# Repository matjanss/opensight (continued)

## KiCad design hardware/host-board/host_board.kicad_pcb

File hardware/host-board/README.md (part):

# Host board v0.3: schematic and board

The host board for the acoustic target: a NodeMCU-32S, 8 sensor connectors, the IR curtain emitter and receiver, an air sensor (BME280 or DS18B20), and the panel LED and button. Every part is through-hole and hand-soldered. The board is 76 × 132 mm (the long side runs north–south), 2 layers, 1.6 mm thick, with an M3 mounting hole in each corner.

The files are in KiCad 10 format; open them with KiCad 10 or newer. "Update PCB from Schematic" reports no changes.

**Not ordered yet; ready to order** (2026-11-24). The two changes below are on the board now,
and the south half was laid out again with them (see [Layout](#layout)):

1. J5 takes a BME280 as well as the DS18B20. See [A BME280 on J5](#1-a-bme280-on-j5).
2. The curtain comparator U4 has a supply jumper: 3.3 V for a TLC372, 5 V for an LM393, with its own decoupling. See [The curtain comparator's supply](#2-the-curtain-comparators-supply-33-v-or-5-v-by-a-jumper).

## Changes before ordering (done)

### 1. A BME280 on J5

**Why:** the speed of sound depends on humidity as well as temperature:

- 0.011 m/s per % RH at 18 °C, and 0.017 at 25 °C;
- 30 → 60 % RH is about 0.08 mm rms of shot position (0.12 mm at 25 °C);
- pressure has almost no effect (100 hPa ≈ 0.01 mm).

The DS18B20 can't see humidity. A BME280 (temperature, humidity and pressure, over I2C) can. Its temperature is no more accurate than the DS18B20's (±0.5 °C); humidity is the gain. See `../../PLAN.md` (D8).

**The change:**

1. **J5:** a 4-pin JST XH (B4B-XH-A) instead of the 3-pin. Pins 1–3 stay as they are, so a DS18B20 cable still plugs into pins 1–3.

   | J5 pin | Now (v0.3) | New |
   |---|---|---|
   | 1 | GND | GND |
   | 2 | DQ: GPIO 14 (U2 pin 12) | SDA, or the DS18B20's DQ: GPIO 14 (U2 pin 12) |
   | 3 | +3V3 (the NodeMCU's 3V3, U2 pin 1) | +3V3 (unchanged) |
   | 4 | – | SCL: GPIO 15 (U2 pin 35) |

2. **R45, new:** 4.7 k from +3V3 to GPIO 15, the SCL pull-up, next to R43. R43 (4.7 k, +3V3 to GPIO 14) stays: it is the SDA pull-up, and the DS18B20's pull-up.
3. **GPIO 12 stays unconnected, with no pull-up.** The firmware moves the pulse generator's sync loopback from GPIO 15 to GPIO 12. GPIO 12 is the flash-voltage strapping pin: anything holding it high at boot stops the module from starting.
4. **Silkscreen:** J5 "BME280 / DS18B20", with pin labels GND, SDA, 3V3, SCL.
5. **Status (2026-11-23):** done in the schematic and the parts list. J5 has its own symbol,
   `CONN4_AIR` (pins GND, SDA/DQ, VDD, SCL), in `host_board.kicad_sym`; the net DQ is now
   `SDA_DQ`, and GPIO 15 is on the new net `SCL`. R45 has R43's footprint (horizontal,
   7.62 mm). ERC: 0 violations. **On the board (2026-11-24):** J5's 4-pin footprint beside J6
   and J7, turned so pin 1 (GND) is at its east end; R45 under the NodeMCU between R43 and
   R44; the silkscreen; the PDFs.

**The sensor and its cable:**

- A BME280 breakout (GY-BME280 or similar), run from 3.3 V.
- Buy carefully: many "BME280" modules are really BMP280s, which have no humidity. The firmware reports the chip ID: 0x60 is a BME280, 0x58 a BMP280.
- Breakouts usually have the pin order VCC, GND, SCL, SDA, which doesn't match J5 one to one: wire the cable by signal name.
- Keep the cable short, up to about 50 cm (I2C at 100 kHz). Many breakouts have their own 10 k pull-ups; with R43 and R45 in parallel that's about 3.2 k, which is fine.
- Mount the sensor in the air between the mics, away from the host board and the IR LEDs, which warm it.

**Firmware:** done in measurement step 3a. The sync loopback is on GPIO 12 (`SYNC_PIN` in
`config.h`); `airtemp.cpp` looks for a BME280 or BMP280 on I2C (SDA 14, SCL 15), else a
DS18B20 on GPIO 14; the speed of sound has the humidity term. Its bench tests with the real
sensors (MEASUREMENT 3a-3, 3a-4) wait for the parts.

### 2. The curtain comparator's supply: 3.3 V or 5 V, by a jumper

**Why:** U4 runs from VA_IR, 3.3 V. Its inputs have to work up to the threshold: RV1 sets
VTH_IR to 1.71–2.35 V (R41 1.5 k, RV1 1 k, R42 2.7 k), and VMID_IR is 1.65 V. When a shadow
lifts the + input past a threshold that is out of the input range, both inputs are out of
range at the crossing, and the comparator's output isn't guaranteed: it can switch late or
not at all.

- **The LM393** (as designed): inputs up to Vcc − 1.5 V, so 1.8 V at 3.3 V (25 °C; Vcc − 2.0
  V = 1.3 V over its temperature range). All but the bottom 90 mV of RV1's travel is out of
  range, and VMID_IR is only 0.15 V below the limit. **At 3.3 V the LM393 doesn't work.**
- **The TLC372CP** (TI CMOS, LM393 pinout, open drain, 200 ns, €1.95 at Okaphone): inputs up
  to Vdd − 1 V at 25 °C, so 2.3 V at 3.3 V; about 2.1–2.3 V at 15–25 °C indoors. TI
  guarantees only Vdd − 1.5 V (1.8 V) over its 0–70 °C range, and characterises it at 5 V
  (it is rated from 3 V). At 3.3 V it works with TP6 (VTH_IR) up to about 2.1 V: VMID_IR +
  450 mV, most of RV1's travel.
- **A TLV3202 on a SOIC-8 to DIP-8 adapter** (the sensor board's comparator: inputs beyond
  both rails, push-pull, 40 ns, 2.7–5.5 V, the LM393's pinout) works at 3.3 V without limits.
  It isn't sold by Dutch shops: it comes from LCSC.

So U4's supply gets a jumper: **3.3 V** for the TLC372 (or the TLV3202), **5 V** for the
LM393. Start with the TLC372 at 3.3 V; if RV1's sweep on the bench (see [TODO.md](TODO.md))
shows it running out of input range, plug in an LM393 and move the jumper to 5 V. See
[Buying U3 and U4](#buying-u3-and-u4-in-the-netherlands) for the parts.

**The change:**

1. **JP1, new:** a 1x3 pin header (2.54 mm) with a jumper shunt, next to U4. Its middle pin
   is U4 pin 8 (V+, a new net `VU4`):
   - pin 1: **VA_IR** (3.3 V): the TLC372, or the TLV3202;
   - pin 3: **VCMP** (about 4.7 V, below): the LM393.

   Silkscreen: "U4 SUPPLY", with "3V3 (TLC372)" and "5V (LM393)" at the ends.
2. **VCMP, a new net** fed from 5V_F (the LP2950's input, after the Schottky):
   - **R46, new:** 10 Ω from 5V_F to VCMP;
   - **C18, new:** 10 µF electrolytic from VCMP to AGND.

   With R46 that is a 1.6 kHz low-pass against the USB rail's noise.
3. **C17 moves with pin 8:** it is U4's 100 nF already (pin 8 to pin 4, AGND), so it now
   decouples VU4, whichever supply is chosen. No new capacitor.
4. **Everything else stays on VA_IR:** U3, VMID_IR, the threshold divider and RV1, and C16
   (U3's 100 nF). The threshold always comes from the quiet 3.3 V.
5. **The output stays as it is:** open collector (LM393) or open drain (TLC372), pulled up to
   +3V3 by R40, so GPIO 13 never sees more than 3.3 V. With a push-pull part (the TLV3202) R40
   only draws 0.33 mA while the output is low, but then the jumper must be at 3.3 V: a
   push-pull output at 5 V would drive GPIO 13 to 5 V. R39 (1 M, the hysteresis) and R38
   are unchanged.
6. **U4 unit B (unused)** stays as it is: + (pin 5) at AGND, − (pin 6) at VA_IR, output (pin
   7) open. Its inputs are inside the range of each part at either supply, except the LM393
   at 3.3 V, which isn't used.
7. **Status (2026-11-23):** done in the schematic and the parts list. JP1 has its own symbol,
   `JMP1x3` (a 1x3 header with the pins named 3V3, U4, 5V), in `host_board.kicad_sym`. ERC: 0
   violations. U4's value is now TLC372. **On the board (2026-11-24):** R46 beside NT1 where
   the supplies cross into AGND, JP1 north of U4 with C18, C17 at U4's pin 8; the
   silkscreen; the PDFs.

**The ranges, per setting:**

| U4 | Jumper | Inputs work up to | RV1's travel (TP6 1.71–2.35 V) |
|---|---|---|---|
| TLC372CP | 3.3 V | about 2.3 V (25 °C), 1.8 V guaranteed (0–70 °C) | up to about 2.1 V: most of it |
| TLV3202 on an adapter | 3.3 V (never 5 V) | 3.5 V | all |
| LM393N | 5 V | about 2.9–3.5 V (25 °C), 2.4–3.0 V over temperature (VCMP 4.4–5.0 V: USB 4.75–5.25 V less the Schottky) | all |
| LM393N | 3.3 V | 1.8 V | **don't use** |

The amplifier's output can reach 3.3 V, above some of these ranges. That's fine: the output
stays right as long as one input (here the threshold) is inside the range. No input goes above
U4's supply.

**Speed:** fast enough with each. The chain from a shadow to IR_IN rising is about 3–8 µs:
the TIA about 1 µs, the ×21 stage about 3.3 µs (τ; the MCP6002's 1 MHz is the slowest part),
the comparator 0.2 µs (TLC372, 10 mV overdrive) or 0.3–1.3 µs (LM393, faster with more
overdrive), R40's rise about 0.2 µs. That delay moves every dip later, so the curtain's window
(`curtain window`, 45–100 µs now) is set from the bench test of the real curtain; a slow air
pistol pellet (150 m/s) is already at 100 µs.

**Also note:** C13 (3.3 nF) into R35 (10 k) is a 33 µs high-pass. During a 30–40 µs shadow the
signal sinks back toward VMID_IR, so the comparator falls early: the dip lengths in the
firmware's `rec` lines (`ir=rise/len`) are shorter than the real shadow. The rise, which the
gate uses, is not affected.

## Changes from v0.2

- The BAT85 clamp diodes are gone; the ESP32's own input clamps and the 470 Ω series resistors protect the inputs.
- The 1x20 debug row (J8) is replaced by a 1x3 scope header per channel (J21–J28: H, GND, L), next to the channel's resistors.
- New GPIO map: the H line of each channel is on the northern pin of its pair, so no line crosses another between the module and the connector.
- IR_EN moved from GPIO16 to GPIO27, DQ (DS18B20) from GPIO17 to GPIO14.
- Rectangular board with a new layout (below).

## Files

- `host_board.kicad_pro`, `.kicad_sch`, `.kicad_pcb`: the project, the schematic (one A2 sheet) and the board.
- `host_board_schematic.pdf`: the schematic as a PDF.
- `host_board_assembly.pdf`: the assembly drawing, with every reference on its part (for soldering).
- Gerbers and drill files are not in the repo: plot them from the board in KiCad when ordering (they are made from it, and go stale with every change to it).
- `host_board_parts_list.csv`: every part, with how many to fit for a 6-channel first build.
- `host_board.pretty/`: the NodeMCU-32S footprint (two 1x19 sockets, rows 22.86 mm apart, from your 23.53 mm measurement over the outside of the pins).
- `host_board.3dshapes/`: the NodeMCU-32S on its sockets as a 3D model (boxes, made by `make_nodemcu.py`), used by U2's footprint.
- `mechanical/`: the board as STEP and STL for the enclosure, with the sizes that matter (see its README).

## Layout

North is the antenna end of the NodeMCU. The north half (the module and the eight channels)
is as it was; the south half was laid out again on 2026-11-24, 14 mm longer, for the J5 and
U4-supply changes and with room for 0.4 mm tracks.

| Where | What |
|---|---|
| Middle, north half | The NodeMCU-32S on sockets, antenna at the north edge, USB plug pointing south (the area south of it is kept free for the plug). No copper under the antenna (a keep-out on both layers) |
| West edge | Sensors CH1–CH4 (J11–J14), north to south. Beside each one: scope header J2n and the four channel resistors |
| East edge | Sensors CH5–CH8 (J15–J18), mirrored |
| Under the NodeMCU | R43 (SDA pull-up), R45 (SCL pull-up), R44 (panel LED), lying flat |
| South of the module, west | The sensor supply: R1 and C3/C4 (5 V filter), U1 LP2950, C5/C6, TP2 (VSENS). R40 (IR_IN pull-up). Then the row where the supplies cross into the receiver's AGND: R30 (VA_IR), NT1 (the ground link), R46 (VCMP) |
| South of the module, east | J6 panel LED and J7 panel button, J5 air sensor (BME280 / DS18B20) below them |
| South-west | IR receiver on its own AGND copper, outlined: U4 (comparator) with JP1, C17, C18 and the threshold (RV1, TP6) in the north; U3 (TIA and ×21 stage) in the south, with J4 photodiodes at the south edge. Test loops TP3 AGND, TP4 TIA, TP5 AMP, TP6 VTH |
| East, south of CH8 | Power: J1 5 V in and J2 panel switch on the east edge, D1, C1, C2, test loops TP1 (+5V), TP7 (GND) |
| South-east | IR emitter: four current limiters side by side (R2.2k, BC337, BC547, R22 each), R29, C7, J3 IR LEDs at the south edge |

Connector pinout (every sensor connector the same way round): VA at the south end, then G, L, G, H at the north end. The scope header pins H, G, L sit level with connector pins H, G, L.

- **Under the NodeMCU:** R43, R44 and R45 are mounted flat there. Solder them before you fit the sockets.
- **Sensor supply:** VSENS runs down each edge outside the sensor connectors, with a stub to
  each VA pin; the two buses meet at TP2 beside U1.
- **Ground:** GND is poured on both sides. The IR receiver has its own AGND pour, joined to GND only at NT1, a wire link or 0 Ω resistor on the north edge of the receiver area. Only the receiver's supplies (VA_IR through R30, VCMP through R46) and IR_IN cross that edge; no other net runs over the AGND copper.
- **Tracks:** 0.4 mm for signals; 0.6 mm for +3V3, VSENS, VA_IR, 5V_F, VCMP and VU4; 0.8 mm
  for VIN, VSW and +5V. Clearance 0.2 mm, vias 0.8/0.4 mm (the net classes in the project).

## Notes for assembly

- **Scope headers:** J21–J28 are optional; fit one when you want to probe a channel.
- **470 Ω resistors:** a wire link can replace any of them.
- **Standing parts:** resistors stand upright on a 2.54 mm pitch to fit 8 channels on the board.
- **Sockets:** use DIP-8 sockets for U3 (MCP6002) and U4 (TLC372, or LM393 with JP1 at 5 V), so either can be swapped (see [Buying U3 and U4](#buying-u3-and-u4-in-the-netherlands)).
- **NodeMCU sockets:** fit the two 1x19 female headers last.

## Buying U3 and U4 in the Netherlands

The curtain receiver's two ICs are both socketed, so a part can be swapped and compared on
the bench. These are the DIP-8 parts found at consumer shops on 2026-11-23. Prices include
21 % VAT. Prices and stock change: check the shop's page before ordering. Okaphone's site
blocks automated visits, so its prices come from search results.

### U3: the op-amp (TIA and ×21 stage)

**Needs:** a dual in DIP-8 with the standard pinout, running from 3.3 V (VA_IR), with a
rail-to-rail output. The TIA's output sits below VMID_IR in steady light, and the ×21
stage's output rises toward 3.3 V on a shadow.

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
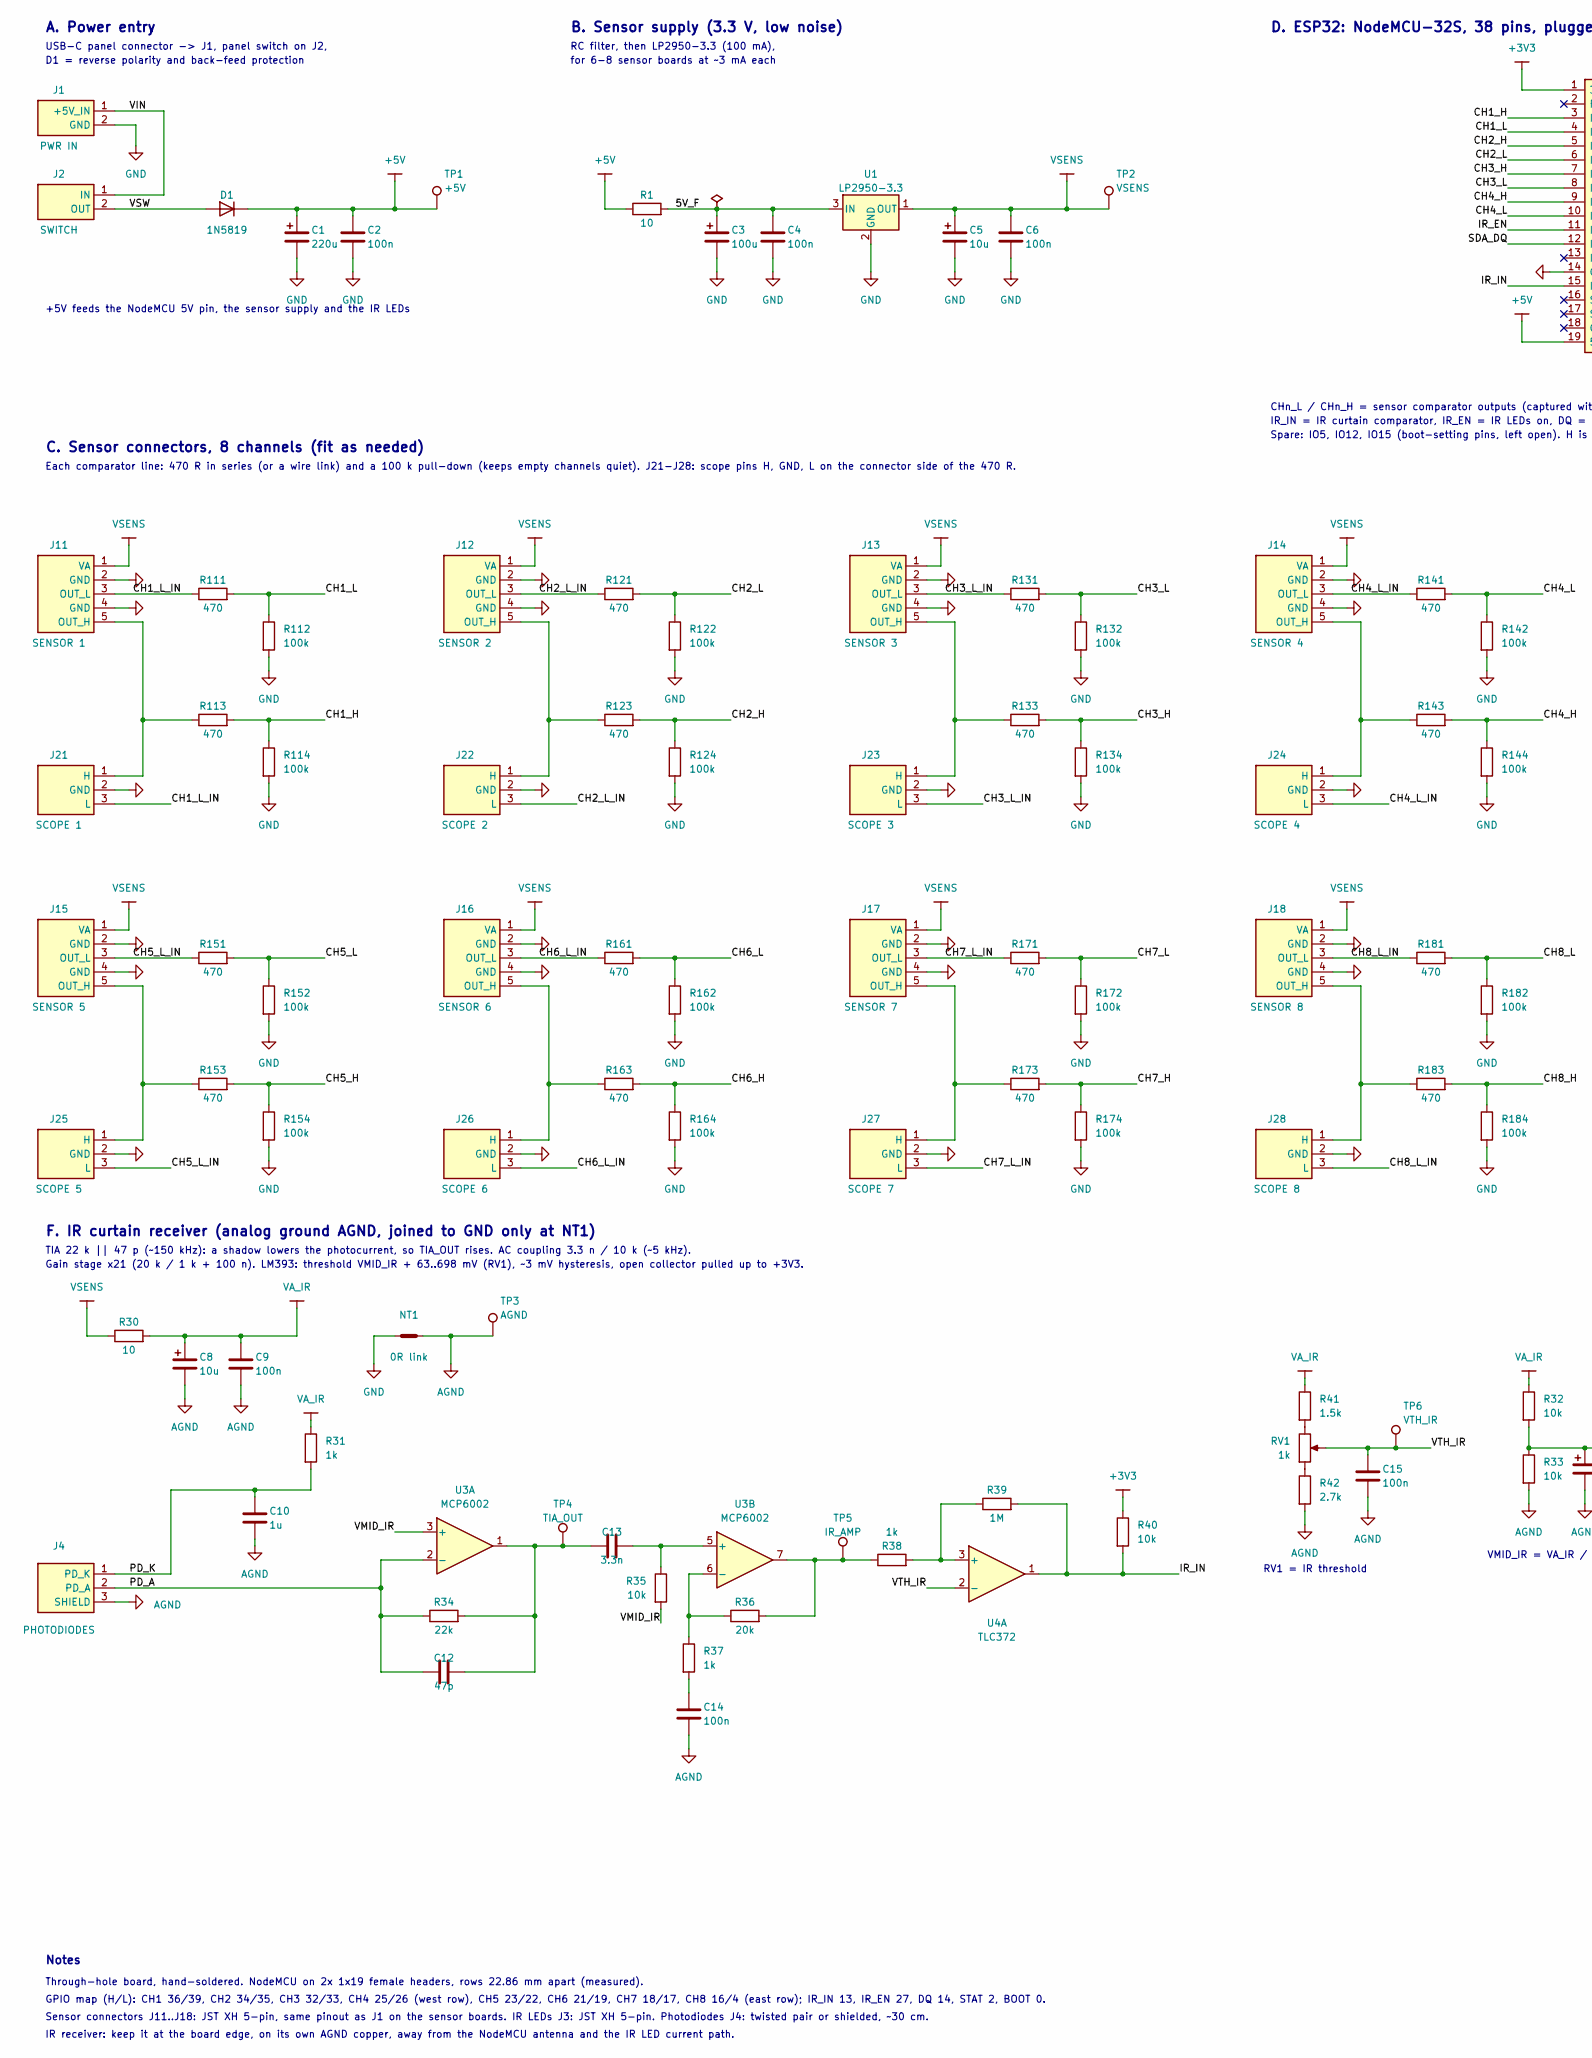
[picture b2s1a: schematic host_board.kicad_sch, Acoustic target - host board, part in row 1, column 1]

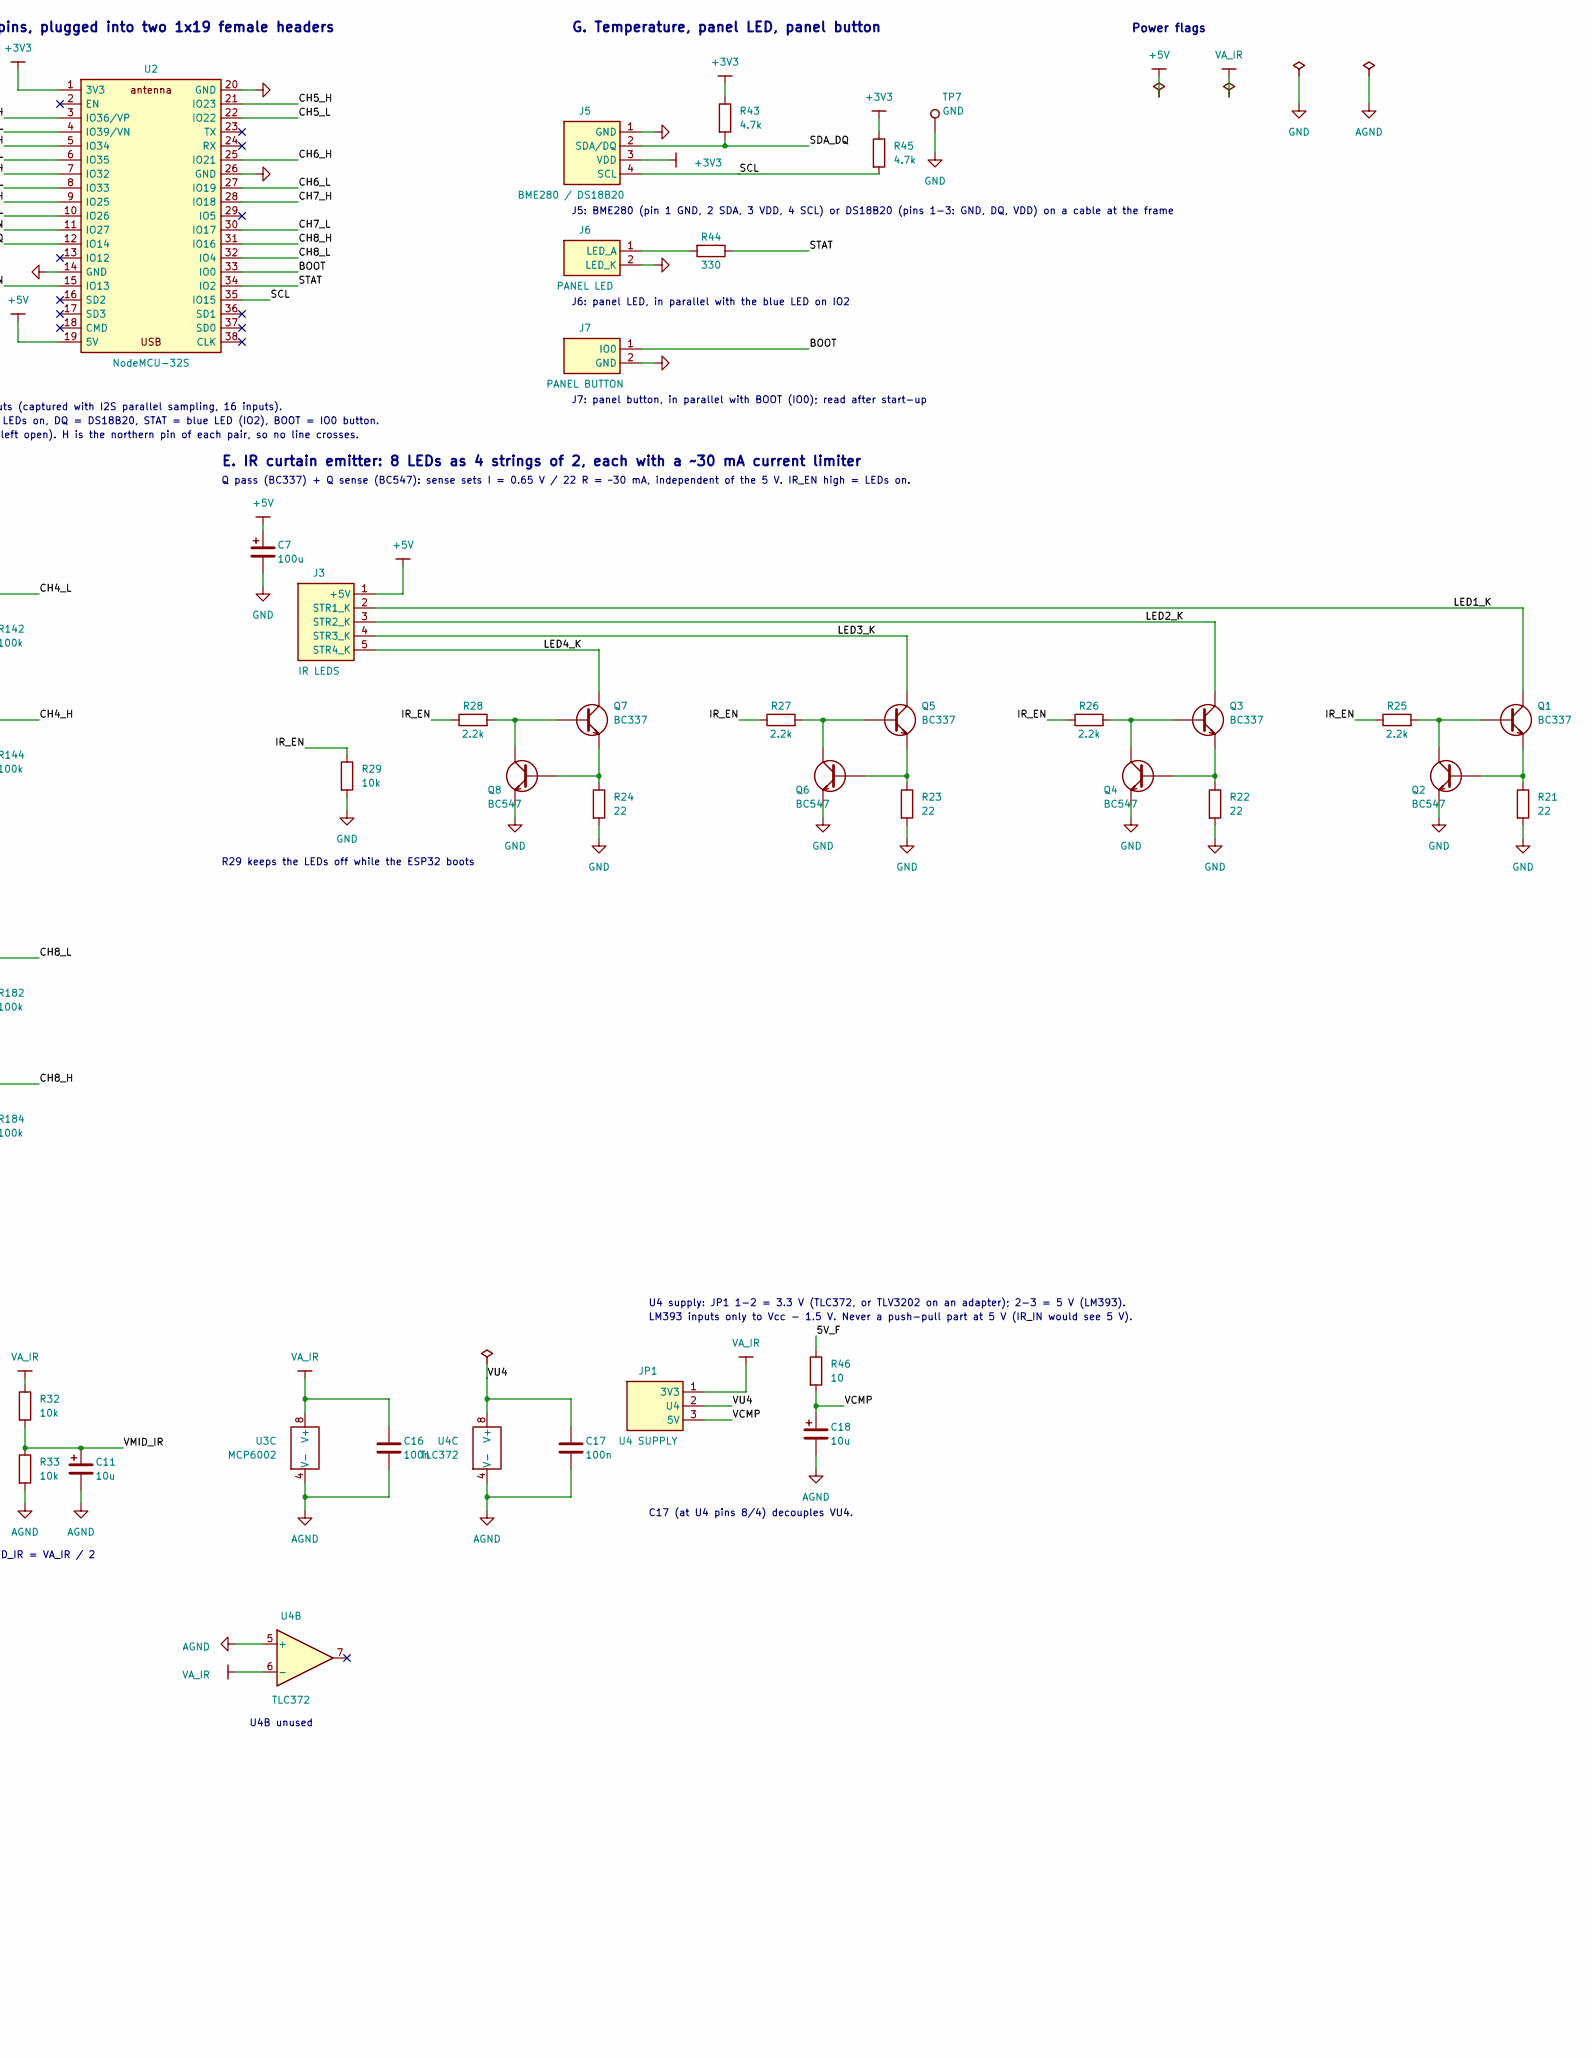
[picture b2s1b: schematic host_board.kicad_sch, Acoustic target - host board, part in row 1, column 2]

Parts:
C1: 220u; CP_Radial_D6.3mm_P2.50mm
C2, C4, C6, C9, C14, C15, C16, C17: 100n; C_Disc_D5.0mm_W2.5mm_P2.50mm
C3, C7: 100u; CP_Radial_D5.0mm_P2.00mm
C5, C8, C11, C18: 10u; CP_Radial_D5.0mm_P2.00mm
C10: 1u; C_Disc_D5.0mm_W2.5mm_P2.50mm
C12: 47p; C_Disc_D5.0mm_W2.5mm_P2.50mm
C13: 3.3n; C_Disc_D5.0mm_W2.5mm_P2.50mm
D1: 1N5819; D_DO-41_SOD81_P10.16mm_Horizontal
J1: PWR IN; JST_XH_B2B-XH-A_1x02_P2.50mm_Vertical
J2: SWITCH; JST_XH_B2B-XH-A_1x02_P2.50mm_Vertical
J3: IR LEDS; JST_XH_B5B-XH-A_1x05_P2.50mm_Vertical
J4: PHOTODIODES; JST_XH_B3B-XH-A_1x03_P2.50mm_Vertical
J5: BME280 / DS18B20; JST_XH_B4B-XH-A_1x04_P2.50mm_Vertical
J6: PANEL LED; JST_XH_B2B-XH-A_1x02_P2.50mm_Vertical
J7: PANEL BUTTON; JST_XH_B2B-XH-A_1x02_P2.50mm_Vertical
J11: SENSOR 1; JST_XH_B5B-XH-A_1x05_P2.50mm_Vertical
J12: SENSOR 2; JST_XH_B5B-XH-A_1x05_P2.50mm_Vertical
J13: SENSOR 3; JST_XH_B5B-XH-A_1x05_P2.50mm_Vertical
J14: SENSOR 4; JST_XH_B5B-XH-A_1x05_P2.50mm_Vertical
J15: SENSOR 5; JST_XH_B5B-XH-A_1x05_P2.50mm_Vertical
J16: SENSOR 6; JST_XH_B5B-XH-A_1x05_P2.50mm_Vertical
J17: SENSOR 7; JST_XH_B5B-XH-A_1x05_P2.50mm_Vertical
J18: SENSOR 8; JST_XH_B5B-XH-A_1x05_P2.50mm_Vertical
J21: SCOPE 1; PinHeader_1x03_P2.54mm_Vertical
J22: SCOPE 2; PinHeader_1x03_P2.54mm_Vertical
J23: SCOPE 3; PinHeader_1x03_P2.54mm_Vertical
J24: SCOPE 4; PinHeader_1x03_P2.54mm_Vertical
J25: SCOPE 5; PinHeader_1x03_P2.54mm_Vertical
J26: SCOPE 6; PinHeader_1x03_P2.54mm_Vertical
J27: SCOPE 7; PinHeader_1x03_P2.54mm_Vertical
J28: SCOPE 8; PinHeader_1x03_P2.54mm_Vertical
JP1: U4 SUPPLY; PinHeader_1x03_P2.54mm_Vertical
NT1: 0R link; R_Axial_DIN0207_L6.3mm_D2.5mm_P2.54mm_Vertical
Q1, Q3, Q5, Q7: BC337; TO-92_Inline
Q2, Q4, Q6, Q8: BC547; TO-92_Inline
R1, R30, R46: 10; R_Axial_DIN0207_L6.3mm_D2.5mm_P2.54mm_Vertical
R21, R22, R23, R24: 22; R_Axial_DIN0207_L6.3mm_D2.5mm_P2.54mm_Vertical
R25, R26, R27, R28: 2.2k; R_Axial_DIN0207_L6.3mm_D2.5mm_P2.54mm_Vertical
R29, R32, R33, R35, R40: 10k; R_Axial_DIN0207_L6.3mm_D2.5mm_P2.54mm_Vertical
R31, R37, R38: 1k; R_Axial_DIN0207_L6.3mm_D2.5mm_P2.54mm_Vertical
R34: 22k; R_Axial_DIN0207_L6.3mm_D2.5mm_P2.54mm_Vertical
R36: 20k; R_Axial_DIN0207_L6.3mm_D2.5mm_P2.54mm_Vertical
R39: 1M; R_Axial_DIN0207_L6.3mm_D2.5mm_P2.54mm_Vertical
R41: 1.5k; R_Axial_DIN0207_L6.3mm_D2.5mm_P2.54mm_Vertical
R42: 2.7k; R_Axial_DIN0207_L6.3mm_D2.5mm_P2.54mm_Vertical
R43, R45: 4.7k; R_Axial_DIN0207_L6.3mm_D2.5mm_P7.62mm_Horizontal
R44: 330; R_Axial_DIN0207_L6.3mm_D2.5mm_P7.62mm_Horizontal
R111, R113, R121, R123, R131, R133, R141, R143, R151, R153, R161, R163, R171, R173, R181, R183: 470; R_Axial_DIN0207_L6.3mm_D2.5mm_P2.54mm_Vertical
R112, R114, R122, R124, R132, R134, R142, R144, R152, R154, R162, R164, R172, R174, R182, R184: 100k; R_Axial_DIN0207_L6.3mm_D2.5mm_P2.54mm_Vertical
RV1: 1k; Potentiometer_Bourns_3296W_Vertical
TP1: +5V; TestPoint_Keystone_5000-5004_Miniature
TP2: VSENS; TestPoint_Keystone_5000-5004_Miniature
TP3: AGND; TestPoint_Keystone_5000-5004_Miniature
TP4: TIA_OUT; TestPoint_Keystone_5000-5004_Miniature
TP5: IR_AMP; TestPoint_Keystone_5000-5004_Miniature
TP6: VTH_IR; TestPoint_Keystone_5000-5004_Miniature
TP7: GND; TestPoint_Keystone_5000-5004_Miniature
U1: LP2950-3.3; TO-92_Inline
U2: NodeMCU-32S; NodeMCU-32S_38pin_Sockets_W22.86mm
U3: MCP6002; DIP-8_W7.62mm_Socket
U4: TLC372; DIP-8_W7.62mm_Socket

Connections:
+3V3: J5.3 (VDD), R40.1, R43.1, R45.1, U2.1 (3V3)
+5V: C1.1 (+), C2.1, C7.1 (+), D1.1 (K), J3.1 (+5V), R1.1, TP1.1 (1_1), U2.19 (5V)
/5V_F: C3.1 (+), C4.1, R1.2, R46.1, U1.3 (IN)
/BOOT: J7.1 (IO0), U2.33 (IO0)
/CH1_H: R113.2, R114.1, U2.3 (IO36/VP)
/CH1_L: R111.2, R112.1, U2.4 (IO39/VN)
/CH1_L_IN: J11.3 (OUT_L), J21.3 (L), R111.1
/CH2_H: R123.2, R124.1, U2.5 (IO34)
/CH2_L: R121.2, R122.1, U2.6 (IO35)
/CH2_L_IN: J12.3 (OUT_L), J22.3 (L), R121.1
/CH3_H: R133.2, R134.1, U2.7 (IO32)
/CH3_L: R131.2, R132.1, U2.8 (IO33)
/CH3_L_IN: J13.3 (OUT_L), J23.3 (L), R131.1
/CH4_H: R143.2, R144.1, U2.9 (IO25)
/CH4_L: R141.2, R142.1, U2.10 (IO26)
/CH4_L_IN: J14.3 (OUT_L), J24.3 (L), R141.1
/CH5_H: R153.2, R154.1, U2.21 (IO23)
/CH5_L: R151.2, R152.1, U2.22 (IO22)
/CH5_L_IN: J15.3 (OUT_L), J25.3 (L), R151.1
/CH6_H: R163.2, R164.1, U2.25 (IO21)
/CH6_L: R161.2, R162.1, U2.27 (IO19)
/CH6_L_IN: J16.3 (OUT_L), J26.3 (L), R161.1
/CH7_H: R173.2, R174.1, U2.28 (IO18)
/CH7_L: R171.2, R172.1, U2.30 (IO17)
/CH7_L_IN: J17.3 (OUT_L), J27.3 (L), R171.1
/CH8_H: R183.2, R184.1, U2.31 (IO16)
/CH8_L: R181.2, R182.1, U2.32 (IO4)
/CH8_L_IN: J18.3 (OUT_L), J28.3 (L), R181.1
/IR_EN: R25.1, R26.1, R27.1, R28.1, R29.1, U2.11 (IO27)
/IR_IN: R39.2, R40.2, U2.15 (IO13), U4.1
/LED1_K: J3.2 (STR1_K), Q1.1 (C)
/LED2_K: J3.3 (STR2_K), Q3.1 (C)
/LED3_K: J3.4 (STR3_K), Q5.1 (C)
/LED4_K: J3.5 (STR4_K), Q7.1 (C)
/PD_A: C12.1, J4.2 (PD_A), R34.1, U3.2 (-)
/PD_K: C10.1, J4.1 (PD_K), R31.2
/SCL: J5.4 (SCL), R45.2, U2.35 (IO15)
/SDA_DQ: J5.2 (SDA/DQ), R43.2, U2.12 (IO14)
/STAT: R44.1, U2.34 (IO2)
/VCMP: C18.1 (+), JP1.3 (5V), R46.2
/VIN: J1.1 (+5V_IN), J2.1 (IN)
/VMID_IR: C11.1 (+), R32.2, R33.1, R35.2, U3.3 (+)
/VSW: D1.2 (A), J2.2 (OUT)
/VTH_IR: C15.1, RV1.2, TP6.1 (1_1), U4.2 (-)
/VU4: C17.1, JP1.2 (U4), U4.8 (V+)
AGND: C8.2 (-), C9.2, C10.2, C11.2 (-), C14.2, C15.2, C16.2, C17.2, C18.2 (-), J4.3 (SHIELD), NT1.2, R33.2, R42.2, TP3.1 (1_1), U3.4 (V-), U4.4 (V-), U4.5 (+)
GND: C1.2 (-), C2.2, C3.2 (-), C4.2, C5.2 (-), C6.2, C7.2 (-), J1.2 (GND), J5.1 (GND), J6.2 (LED_K), J7.2 (GND), J11.2 (GND), J11.4 (GND), J12.2 (GND), J12.4 (GND), J13.2 (GND), J13.4 (GND), J14.2 (GND), J14.4 (GND), J15.2 (GND), J15.4 (GND), J16.2 (GND), J16.4 (GND), J17.2 (GND), J17.4 (GND), J18.2 (GND), J18.4 (GND), J21.2 (GND), J22.2 (GND), J23.2 (GND), J24.2 (GND), J25.2 (GND), J26.2 (GND), J27.2 (GND), J28.2 (GND), NT1.1, Q2.3 (E), Q4.3 (E), Q6.3 (E), Q8.3 (E), R21.2, R22.2, R23.2, R24.2, R29.2, R112.2, R114.2, R122.2, R124.2, R132.2, R134.2, R142.2, R144.2, R152.2, R154.2, R162.2, R164.2, R172.2, R174.2, R182.2, R184.2, TP7.1 (1_1), U1.2 (GND), U2.14 (GND), U2.20 (GND), U2.26 (GND)
unnamed: C12.2, C13.1, R34.2, TP4.1 (1_1), U3.1
unnamed: C14.1, R37.2
unnamed: J6.1 (LED_A), R44.2
unnamed: J11.5 (OUT_H), J21.1 (H), R113.1
unnamed: J12.5 (OUT_H), J22.1 (H), R123.1
unnamed: J13.5 (OUT_H), J23.1 (H), R133.1
unnamed: J14.5 (OUT_H), J24.1 (H), R143.1
unnamed: J15.5 (OUT_H), J25.1 (H), R153.1
unnamed: J16.5 (OUT_H), J26.1 (H), R163.1
unnamed: J17.5 (OUT_H), J27.1 (H), R173.1
unnamed: J18.5 (OUT_H), J28.1 (H), R183.1
unnamed: Q1.2 (B), Q2.1 (C), R25.2
unnamed: Q1.3 (E), Q2.2 (B), R21.1
unnamed: Q3.2 (B), Q4.1 (C), R26.2
unnamed: Q3.3 (E), Q4.2 (B), R22.1
unnamed: Q5.2 (B), Q6.1 (C), R27.2
unnamed: Q5.3 (E), Q6.2 (B), R23.1
unnamed: Q7.2 (B), Q8.1 (C), R28.2
unnamed: Q7.3 (E), Q8.2 (B), R24.1
unnamed: R36.2, R38.1, TP5.1 (1_1), U3.7
unnamed: R41.2, RV1.1
unnamed: R42.1, RV1.3
unnamed: C13.2, R35.1, U3.5 (+)
unnamed: R36.1, R37.1, U3.6 (-)
unnamed: R38.2, R39.1, U4.3 (+)
VA_IR: C8.1 (+), C9.1, C16.1, JP1.1 (3V3), R30.2, R31.1, R32.1, R41.1, U3.8 (V+), U4.6 (-)
VSENS: C5.1 (+), C6.1, J11.1 (VA), J12.1 (VA), J13.1 (VA), J14.1 (VA), J15.1 (VA), J16.1 (VA), J17.1 (VA), J18.1 (VA), R30.1, TP2.1 (1_1), U1.1 (OUT)

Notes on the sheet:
Through-hole board, hand-soldered. NodeMCU on 2x 1x19 female headers, rows 22.86 mm apart (measured).
D1 = reverse polarity and back-feed protection
RC filter, then LP2950-3.3 (100 mA),
J6: panel LED, in parallel with the blue LED on IO2
J5: BME280 (pin 1 GND, 2 SDA, 3 VDD, 4 SCL) or DS18B20 (pins 1-3: GND, DQ, VDD) on a cable at the frame
Sensor connectors J11..J18: JST XH 5-pin, same pinout as J1 on the sensor boards. IR LEDs J3: JST XH 5-pin. Photodiodes J4: twisted pair or shielded, ~30 cm.
J7: panel button, in parallel with BOOT (IO0); read after start-up
IR receiver: keep it at the board edge, on its own AGND copper, away from the NodeMCU antenna and the IR LED current path.
F. IR curtain receiver (analog ground AGND, joined to GND only at NT1)
D. ESP32: NodeMCU-32S, 38 pins, plugged into two 1x19 female headers
VMID_IR = VA_IR / 2
Spare: IO5, IO12, IO15 (boot-setting pins, left open). H is the northern pin of each pair, so no line crosses.
IR_IN = IR curtain comparator, IR_EN = IR LEDs on, DQ = DS18B20, STAT = blue LED (IO2), BOOT = IO0 button.
CHn_L / CHn_H = sensor comparator outputs (captured with I2S parallel sampling, 16 inputs).
Each comparator line: 470 R in series (or a wire link) and a 100 k pull-down (keeps empty channels quiet). J21-J28: scope pins H, GND, L on the connector side of the 470 R.
+5V feeds the NodeMCU 5V pin, the sensor supply and the IR LEDs
TIA 22 k || 47 p (~150 kHz): a shadow lowers the photocurrent, so TIA_OUT rises. AC coupling 3.3 n / 10 k (~5 kHz).
USB-C panel connector -> J1, panel switch on J2,
R29 keeps the LEDs off while the ESP32 boots
Gain stage x21 (20 k / 1 k + 100 n). LM393: threshold VMID_IR + 63..698 mV (RV1), ~3 mV hysteresis, open collector pulled up to +3V3.
Power flags
Q pass (BC337) + Q sense (BC547): sense sets I = 0.65 V / 22 R = ~30 mA, independent of the 5 V. IR_EN high = LEDs on.
GPIO map (H/L): CH1 36/39, CH2 34/35, CH3 32/33, CH4 25/26 (west row), CH5 23/22, CH6 21/19, CH7 18/17, CH8 16/4 (east row); IR_IN 13, IR_EN 27, DQ 14, STAT 2, BOOT 0.
B. Sensor supply (3.3 V, low noise)
U4B unused
G. Temperature, panel LED, panel button
C. Sensor connectors, 8 channels (fit as needed)
A. Power entry
RV1 = IR threshold
E. IR curtain emitter: 8 LEDs as 4 strings of 2, each with a ~30 mA current limiter
for 6-8 sensor boards at ~3 mA each
Notes
U4 supply: JP1 1-2 = 3.3 V (TLC372, or TLV3202 on an adapter); 2-3 = 5 V (LM393).
LM393 inputs only to Vcc - 1.5 V. Never a push-pull part at 5 V (IR_IN would see 5 V).
C17 (at U4 pins 8/4) decouples VU4.

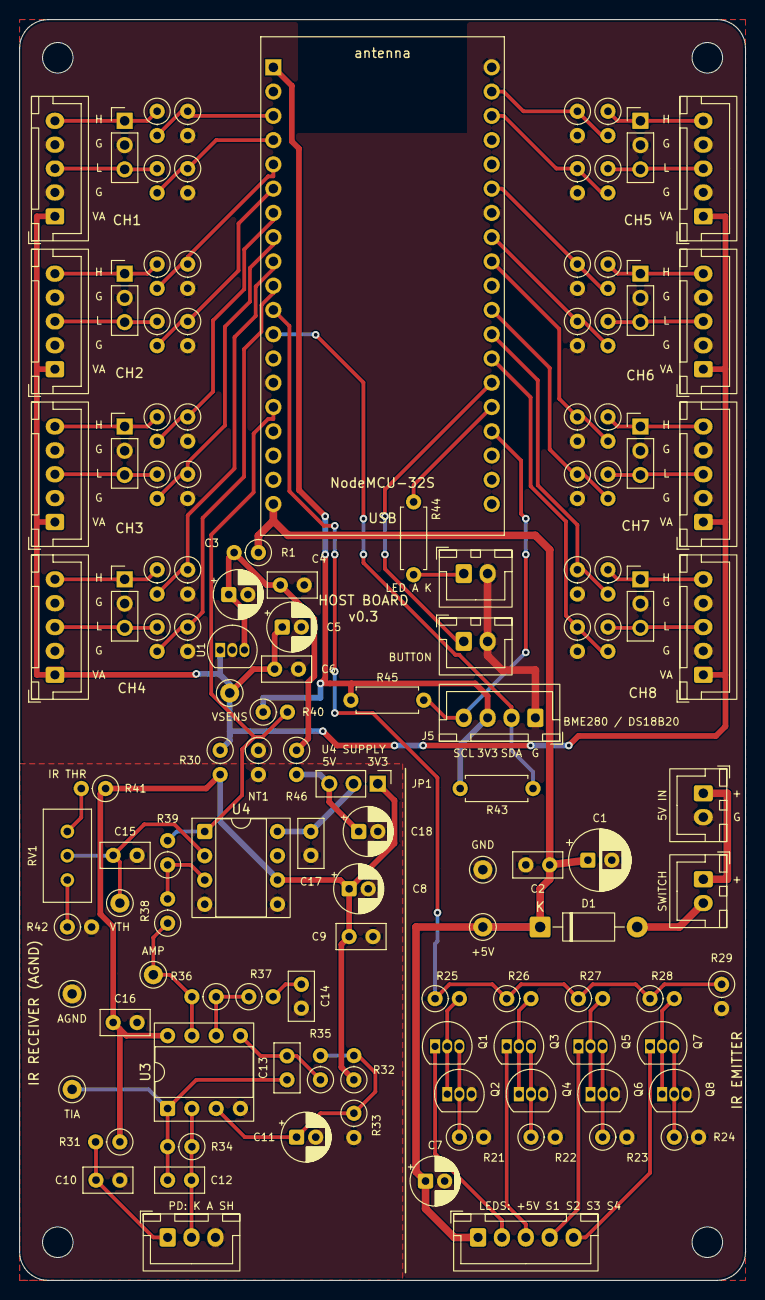
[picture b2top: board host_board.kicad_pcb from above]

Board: 2 copper layers, 76.0 x 132.0 mm, 127 parts (0 on the bottom side), 74 nets.

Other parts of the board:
H1, H2, H3, H4: M3; MountingHole_3.2mm_M3

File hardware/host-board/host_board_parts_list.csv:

References,Value,Part,On board,Fit for a 6-channel first build,Footprint,Notes
J1,PWR IN,JST XH vertical header (+ housing and crimps for the cable),1,1,JST_XH_B2B-XH-A_1x02_P2.50mm_Vertical,from USB-C panel connector
J2,SWITCH,JST XH vertical header (+ housing and crimps for the cable),1,1,JST_XH_B2B-XH-A_1x02_P2.50mm_Vertical,to panel on-off switch
D1,1N5819,diode,1,1,D_DO-41_SOD81_P10.16mm_Horizontal,reverse polarity / back-feed
C1,220u,"electrolytic capacitor, radial",1,1,CP_Radial_D6.3mm_P2.50mm,10 V electrolytic
"C2, C4, C6, C9, C14, C16, C17, C15",100n,"ceramic capacitor, 2.5 mm pitch",8,8,C_Disc_D5.0mm_W2.5mm_P2.50mm,at U3; at U4
TP1,+5V,Keystone 5000-series test loop,1,1,TestPoint_Keystone_5000-5004_Miniature,
"R1, R30, R46",10,"resistor 1/4 W 1 %, standing (2.54 mm)",3,3,R_Axial_DIN0207_L6.3mm_D2.5mm_P2.54mm_Vertical,
"C3, C7",100u,"electrolytic capacitor, radial",2,2,CP_Radial_D5.0mm_P2.00mm,10 V electrolytic
U1,LP2950-3.3,"LP2950ACZ-3.3 low-noise LDO, TO-92",1,1,TO-92_Inline,"LP2950ACZ-3.3, TO-92"
"C5, C8, C11, C18",10u,"electrolytic capacitor, radial",4,4,CP_Radial_D5.0mm_P2.00mm,16 V electrolytic
TP2,VSENS,Keystone 5000-series test loop,1,1,TestPoint_Keystone_5000-5004_Miniature,
"J11, J12, J13, J14, J15, J16, J17, J18",SENSOR 1-8,JST XH vertical header (+ housing and crimps for the cable),8,6,JST_XH_B5B-XH-A_1x05_P2.50mm_Vertical,fit as needed
"J21, J22, J23, J24, J25, J26, J27, J28",SCOPE 1-8,"1x3 pin header, 2.54 mm",8,0,PinHeader_1x03_P2.54mm_Vertical,"scope pins H, GND, L; fit only when needed"
"R111, R113, R121, R123, R131, R133, R141, R143, R151, R153, R161, R163, R171, R173, R181, R183",470,"resistor 1/4 W 1 %, standing (2.54 mm)",16,12,R_Axial_DIN0207_L6.3mm_D2.5mm_P2.54mm_Vertical,or wire link
"R112, R114, R122, R124, R132, R134, R142, R144, R152, R154, R162, R164, R172, R174, R182, R184",100k,"resistor 1/4 W 1 %, standing (2.54 mm)",16,12,R_Axial_DIN0207_L6.3mm_D2.5mm_P2.54mm_Vertical,
U2,NodeMCU-32S,"NodeMCU-32S (ESP32-WROOM-32), 38-pin; plus 2x 1x19 female header, 2.54 mm",1,1,NodeMCU-32S_38pin_Sockets_W22.86mm,plug-in module on 2x 1x19 female headers
J3,IR LEDS,JST XH vertical header (+ housing and crimps for the cable),1,1,JST_XH_B5B-XH-A_1x05_P2.50mm_Vertical,"8 x 940 nm, 4 strings of 2"
"R29, R32, R33, R35, R40",10k,"resistor 1/4 W 1 %, standing (2.54 mm)",5,5,R_Axial_DIN0207_L6.3mm_D2.5mm_P2.54mm_Vertical,"LEDs off during boot; pull-up, open-collector output"
"Q1, Q3, Q5, Q7",BC337,"NPN transistor, TO-92",4,4,TO-92_Inline,pass
"Q2, Q4, Q6, Q8",BC547,"NPN transistor, TO-92",4,4,TO-92_Inline,sense
"R21, R22, R23, R24",22,"resistor 1/4 W 1 %, standing (2.54 mm)",4,4,R_Axial_DIN0207_L6.3mm_D2.5mm_P2.54mm_Vertical,sets ~30 mA
"R25, R26, R27, R28",2.2k,"resistor 1/4 W 1 %, standing (2.54 mm)",4,4,R_Axial_DIN0207_L6.3mm_D2.5mm_P2.54mm_Vertical,
NT1,0R link,wire link or 0 R (AGND-GND join),1,1,R_Axial_DIN0207_L6.3mm_D2.5mm_P2.54mm_Vertical,wire link or 0 R: the single join of AGND to GND
J4,PHOTODIODES,JST XH vertical header (+ housing and crimps for the cable),1,1,JST_XH_B3B-XH-A_1x03_P2.50mm_Vertical,"4x BPW34F in parallel, twisted pair / shield"
"R31, R37, R38",1k,"resistor 1/4 W 1 %, standing (2.54 mm)",3,3,R_Axial_DIN0207_L6.3mm_D2.5mm_P2.54mm_Vertical,
C10,1u,"ceramic capacitor, 2.5 mm pitch",1,1,C_Disc_D5.0mm_W2.5mm_P2.50mm,
U3,MCP6002,"MCP6002-I/P dual op-amp, DIP-8 (+ DIP-8 socket)",1,1,DIP-8_W7.62mm_Socket,MCP602 or MCP6022: pin-compatible and faster (README: Buying U3 and U4)
R34,22k,"resistor 1/4 W 1 %, standing (2.54 mm)",1,1,R_Axial_DIN0207_L6.3mm_D2.5mm_P2.54mm_Vertical,
C12,47p,"ceramic capacitor, 2.5 mm pitch (C0G)",1,1,C_Disc_D5.0mm_W2.5mm_P2.50mm,C0G
C13,3.3n,"ceramic capacitor, 2.5 mm pitch",1,1,C_Disc_D5.0mm_W2.5mm_P2.50mm,
R36,20k,"resistor 1/4 W 1 %, standing (2.54 mm)",1,1,R_Axial_DIN0207_L6.3mm_D2.5mm_P2.54mm_Vertical,
U4,TLC372,"TLC372CP dual comparator (CMOS, open drain), DIP-8 (+ DIP-8 socket)",1,1,DIP-8_W7.62mm_Socket,"JP1 at 3.3 V; or LM393N with JP1 at 5 V (README: U4 supply); unit B unused, output pin 7 open"
JP1,U4 SUPPLY,"1x3 pin header, 2.54 mm, + jumper shunt",1,1,PinHeader_1x03_P2.54mm_Vertical,"U4's supply: 1-2 3.3 V (TLC372, TLV3202), 2-3 5 V (LM393 only)"
R39,1M,"resistor 1/4 W 1 %, standing (2.54 mm)",1,1,R_Axial_DIN0207_L6.3mm_D2.5mm_P2.54mm_Vertical,hysteresis ~3 mV
R41,1.5k,"resistor 1/4 W 1 %, standing (2.54 mm)",1,1,R_Axial_DIN0207_L6.3mm_D2.5mm_P2.54mm_Vertical,
RV1,1k,"Bourns 3296W 1 k, 25-turn",1,1,Potentiometer_Bourns_3296W_Vertical,"25-turn, IR threshold"
R42,2.7k,"resistor 1/4 W 1 %, standing (2.54 mm)",1,1,R_Axial_DIN0207_L6.3mm_D2.5mm_P2.54mm_Vertical,
TP3,AGND,Keystone 5000-series test loop,1,1,TestPoint_Keystone_5000-5004_Miniature,
TP4,TIA_OUT,Keystone 5000-series test loop,1,1,TestPoint_Keystone_5000-5004_Miniature,
TP5,IR_AMP,Keystone 5000-series test loop,1,1,TestPoint_Keystone_5000-5004_Miniature,
TP6,VTH_IR,Keystone 5000-series test loop,1,1,TestPoint_Keystone_5000-5004_Miniature,
J5,BME280 / DS18B20,JST XH vertical header (+ housing and crimps for the cable),1,1,JST_XH_B4B-XH-A_1x04_P2.50mm_Vertical,"cable to the frame: GND, SDA/DQ, VDD, SCL; a DS18B20 uses pins 1-3"
"R43, R45",4.7k,"resistor 1/4 W 1 %, horizontal (7.62 mm)",2,2,R_Axial_DIN0207_L6.3mm_D2.5mm_P7.62mm_Horizontal,"horizontal, under the NodeMCU; R43 SDA/DQ pull-up, R45 SCL pull-up"
J6,PANEL LED,JST XH vertical header (+ housing and crimps for the cable),1,1,JST_XH_B2B-XH-A_1x02_P2.50mm_Vertical,parallel to on-board blue LED (GPIO 2)
R44,330,"resistor 1/4 W 1 %, horizontal (7.62 mm)",1,1,R_Axial_DIN0207_L6.3mm_D2.5mm_P7.62mm_Horizontal,"horizontal, under the NodeMCU"
J7,PANEL BUTTON,JST XH vertical header (+ housing and crimps for the cable),1,1,JST_XH_B2B-XH-A_1x02_P2.50mm_Vertical,parallel to BOOT (GPIO 0)
TP7,GND,Keystone 5000-series test loop,1,1,TestPoint_Keystone_5000-5004_Miniature,
H1-H4,M3,mounting hole 3.2 mm (board only),4,4,MountingHole_3.2mm_M3,

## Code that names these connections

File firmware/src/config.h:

// OpenSights - pins and timings of this board (NodeMCU-32S).
#pragma once
#include <Arduino.h>

const int LED_PIN  = 2;    // onboard blue LED, active high
const int BOOT_BTN_PIN = 0;    // onboard BOOT button to GND (has an external pull-up)

const uint32_t HEARTBEAT_PERIOD_MS = 2000;
const uint32_t DEBOUNCE_MS         = 30;
const uint32_t LONG_PRESS_MS       = 2000;   // hold BOOT this long to enter pairing mode
const uint32_t RESET_PRESS_MS      = 10000;  // ... this long to reset the PIN and delete all bonds
const uint32_t RESET_SIGNAL_MS     = 1500;   // LED stays on this long to confirm the reset
const uint32_t PAIRING_WINDOW_MS   = 60000;  // pairing mode ends after this, or after a pairing
const uint32_t PAIRING_BLINK_MS    = 150;    // LED half-period while in pairing mode
const uint32_t LOOP_PERIOD_MS      = 10;     // button sampling rate; nothing here needs to be faster
const uint32_t SHOT_FLASH_MS       = 80;     // LED flashes this long for every shot

// The shot store (lib/store, MEASUREMENT 5e): every hit in flash, in the `shots` partition
// (partitions.csv: data, subtype 0x40, 128 KB = 1920 hits at least), across reboots. With no
// such partition (an old partition table), a ring in RAM of STORE_RAM_SECTORS sectors.
const uint8_t  STORE_PART_SUBTYPE   = 0x40;
const int      STORE_RAM_SECTORS    = 4;      // the fallback: 4 KB each, 129 hits at least
const uint32_t STORE_QUIET_MS       = 2000;   // erase the sector ahead only after this long
                                              // without a shot or an event (about 45 ms)
const uint32_t SHOT_RETRY_MS        = 500;    // wait after a failed indication before retrying
const int      EVENT_BUFFER         = 32;     // events kept for resending (protocol v3, 180 bytes each)
const uint32_t STATUS_PERIOD_MS     = 500;    // Status is rebuilt this often, notified if it changed
// Test shots (BOOT short press) until there is measuring hardware: normally distributed
// around the centre. 15 mm puts most of them in the 7-10 rings of the air pistol card.
const float    TEST_SHOT_SIGMA_MM   = 15.0f;

// --- Measurement (see ../MEASUREMENT.md) ---
// Comparator lines of host board v0.3 (hardware/host-board/README.md), in I2S data-bit
// order: bit 2n = CH(n+1) OUT_L, bit 2n+1 = CH(n+1) OUT_H. Lines idle low and go high
// while SIG is above the threshold.
constexpr int CAPTURE_LINE_PINS[16] = {
  39, 36,   // CH1
  35, 34,   // CH2
  33, 32,   // CH3
  26, 25,   // CH4
  22, 23,   // CH5
  19, 21,   // CH6
  17, 18,   // CH7
   4, 16,   // CH8
};
const int IR_EN_PIN = 27;   // IR curtain LEDs, high = on (with `curtain on`, step 4b)
const int IR_IN_PIN = 13;   // IR curtain comparator: high while the beam is blocked (step 4b)

// The I2S sample clock is made by LEDC and looped back through this pin (spare on the
// host board; leave it unconnected).
const int      CAPTURE_CLK_PIN        = 5;
const uint32_t CAPTURE_SAMPLE_HZ      = 10000000;   // 100 ns per sample
const int      CAPTURE_BLOCK_BYTES    = 4000;       // per DMA descriptor: 2000 samples, 200 us
const int      CAPTURE_RING_BLOCKS    = 16;         // ring: 64 KB, 3.2 ms
// The event window must hold every mic's first edge. Sound reaches two mics at most
// (distance between them) / (speed of sound) apart, wherever the shot lands, so the window
// follows from the largest distance between two mics (the diagonal for corner mics). It is
// a setting (serial `span`, stored in NVS; later an app setting, see MEASUREMENT.md step 5).
// Default: corner mics just outside a 200 x 200 mm card, about 210 mm apart: 300 mm.
const uint32_t CAPTURE_SPAN_MM_DEFAULT = 300;
const uint32_t SOUND_SPEED_MIN_M_S     = 331;   // at 0 degC: the slowest the window allows for
const uint32_t CAPTURE_WINDOW_MARGIN_PCT = 20;  // on top of span / speed of sound
const uint32_t CAPTURE_WINDOW_EXTRA_US = 100;   // comparator delay on a quiet far mic, pulse end
// The I2S FIFO packs two 16-bit samples per 32-bit word. esp32-camera reads the earlier
// sample from the high half; confirmed on the bench (step 1: pulse lengths exact).
const bool     CAPTURE_HIGH_HALF_FIRST = true;

const uint16_t CAPTURE_MASK_DEFAULT     = 0x0F;   // fitted channels, bit n = CH(n+1)
const uint32_t CAPTURE_DEADTIME_DEFAULT = 30;     // ms after an event with no new event

// Self-test: pulses driven out on CH8's own pins (the I2S reads them back on the same
// pins, so no jumpers are needed). CH8 must have no sensor board plugged in.
constexpr int  SELFTEST_PIN_L       = CAPTURE_LINE_PINS[14];   // CH8 OUT_L, GPIO 4
constexpr int  SELFTEST_PIN_H       = CAPTURE_LINE_PINS[15];   // CH8 OUT_H, GPIO 16
const uint32_t SELFTEST_PULSE_US    = 10;   // OUT_L pulse length; OUT_H ends with it

// The pulse generator (self-test and simulator) starts its MCPWM units from an edge on this
// pin, driven and read back inside the chip: leave it unconnected (spare on the host
// board). A strapping pin (flash voltage: nothing may pull it up at reset), so it is only
// driven after boot and held by a pull-down otherwise. Was GPIO 15 until step 3a; 15 is
// the BME280's SCL now.
const int      SYNC_PIN             = 12;

// --- Step 2 (see ../MEASUREMENT.md) ---
// Arrival time t0 = t1 - k (t2 - t1) - offset; k and the offsets are settings (NVS).
const float    ARRIVAL_K_DEFAULT    = 1.0f / 3;

// --- Step 3c: the solver on the board ---
// The calibration (NVS "cal", calib.cpp): per channel its mic (x, y, h), k, offset and
// sigma. Defaults: the D1/D2 layout on CH1-CH6 (`mic default`).
const float    MIC_H_DEFAULT_MM     = 5.5f;    // mic port behind the paper: the board's edge on it (21.5 flipped)
// The D1/D2 layout (PLAN.md), mm: bottom left, bottom right, top right moved out 25 mm along
// its diagonal (105 + 25/sqrt 2; it was slid 40 mm along the top edge, to (65, 105), before
// 2026-11-24), top left, bottom middle, right middle.
const float    MIC_LAYOUT_D2[6][2]  = {{-105, -105}, {105, -105}, {122.68f, 122.68f}, {-105, 105}, {0, -105}, {105, 0}};
const float    SIGMA_DEFAULT_NS     = 50.0f;   // timing error per channel until calibrated (3e)
// A solved shot goes to the app if the fit converged with an rms residual up to this (ns;
// `reslimit`, stored: measure::RES_LIMIT_DEFAULT_NS). Validity proper is step 4.
const float    CARD_HALF_MM         = 100.0f;  // the scoring area: |x|, |y| up to this

// Simulator (3d): 6 mics on CH3-CH8 (their pins can be outputs; CH1/CH2 are input-only),
// the pulse generator's 6 MCPWM operators: CH3-CH5 on unit 0, CH6-CH8 on unit 1. Its mics
// default to the D1/D2 layout in order: CH3 bottom left, CH4 bottom right, CH5 top right
// (slid), CH6 top left, CH7 bottom middle, CH8 right middle. Those connectors must have no
// sensor board plugged in while it runs.
const int      SIM_FIRST_CHANNEL    = 2;      // CH3, 0-based
const int      SIM_CHANNELS         = 6;
const float    SIM_CARD_MM          = 100.0f; // random shots land within +-this of the centre
const float    SIM_POS_LIMIT_MM     = 0.1f;   // position check: worst error vs the truth (3c)
const float    SIM_POS_LIMIT_DROP_MM = 0.15f; // the same with a faulty channel dropped (5 mics, 3d)

// The air (step 3a): J5 takes a BME280/BMP280 on I2C (SDA, SCL) or a DS18B20 on 1-Wire
// (SDA's pin, read through UART2: the UART times the slots, so no interrupts are held off),
// read by a task on core 0, once a minute. 4.7 k pull-ups to 3V3 on the host board.
const int      AIR_SDA_PIN          = 14;      // also the DS18B20's DQ
const int      AIR_SCL_PIN          = 15;
const uint32_t AIR_TEMP_PERIOD_MS   = 60000;
const uint32_t AIR_PROBE_TRIES      = 3;       // look for a sensor this often, a period apart, then stop
const uint32_t AIR_TEMP_STALE_MS    = 600000;  // no good reading for this long: use the defaults
const float    AIR_TEMP_DEFAULT_C   = 18.0f;   // without a reading
const float    AIR_RH_DEFAULT       = 50.0f;   // % RH, without a BME280
const float    AIR_HPA_DEFAULT      = 1013.25f;   // without a BME280 or BMP280
